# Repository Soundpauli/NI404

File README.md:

DIY OPEN SOURCE HARDWARE SAMPLER-SEQUENCER

---------

IMPORTANT NOTE:

This project, the NI404, is a stale project and is no longer actively maintained. However, it still works and remains an excellent, affordable project for beginners interested in building their own hardware sampler-sequencer. Soldering is required to assemble the NI404. 

For those looking for a more modern alternative, check out the successor project, toern (https://github.com/Soundpauli/toern). The new project offers the option to purchase a self-build kit that doesn't require soldering skills or a fully assembled version. While the NI404 is an older design, feel free to fork the code and contribute to its development if you're interested.

---------

An Etch-A-SketchTM inspired device for beginners and makers.

THE OPEN SOURCE SAMPLE-SEQUENCER FOR EVERYONE.
<<<<<<< HEAD
-------------
The NI404 is an innovative, open-source DIY sample-sequencer from SP_ (aka soundpauli) - inspired by the classic Etch-A-Sketch, tailored for beginners and DIY enthusiasts. Designed around the Teensy Microcontroller and Audioboard from PJRC, this device offers an accessible entry point into the world of music creation.
=======

The NI404 is an innovative, open-source DIY sample-sequencer from SP_ (formaly known as soundpauli) - inspired by the classic Etch-A-Sketch, tailored for beginners and DIY enthusiasts. Designed around the Teensy Microcontroller and Audioboard from PJRC, this device offers an accessible entry point into the world of music creation.
>>>>>>> 7d1964479870bf18bf8a6309d7f64ec11712a006
The NI404 is more than just a musical instrument; it's a journey into the world of sound exploration, perfect for live performances, studio sessions, or simply having fun creating music. Whether you're a seasoned musician or a curious beginner, the NI404 is your gateway to an exciting world of musical possibilities.

EASY TO USE.
-------------
With its playful design, the NI404 lets users create complex sound patterns without any prior knowledge of musical instruments or equipment. It's perfect for beginners and makers alike.

DYNAMIC CONTROL DESPITE LESS BUTTONS.
-------------
At the heart of the NI404 is a vivid 16x16 RGB LED panel display, paired with three intuitive rotary-push encoders. Navigate a cursor across the grid, where each row signifies a voice and each column a potential note, allowing for up to 16 pitches per note. This feature enables the mixing of up to 8 voices simultaneously.

REAL-TIME INTERACTION.
-------------
Adjust samples, instruments, pitches, notes, volume, BPM, velocity, and effects in real-time without pausing. This seamless interaction makes the NI404 an ideal gadget for live performances.

CORE COMPONENTS.
-------------
Teensy 4.1 Microcontroller and Teensy Audio board (4.0)
8MB PSRAM Flash Memory
3 Rotary-push encoders
16x16 RGB-LED Panel driven by FastLED
3.5mm audio jack and removable SD Microcard slot

CREATIVE FLEXIBILITY.
-------------
Etch-A-Sketch style note drawing
On-the-fly note deletion and sample muting
Adjustable volume, BPM (40 - 200), pattern, and note velocity
Up to 30-second sample length with seamless looping
Use your own samples on the SD-Card - in a simple file structure
Load up to 8 voices / samples (Wav format) plus an additional onboard synth voice
16-bar patterns across 8 pages, totaling 128 bars per song
Save and load up to 100 patterns / songs on the SD card
Autosave and autoload functions
SAMPLES AT YOUR FINGERTIPS:
THE BUILT-IN SAMPLE BROWSER.
Access and manage samples while playing, with support for up to 999 samples on the SD card and the ability to predefine multiple voices as a SampleSet.

FULLY INDEPENDENT.
-------------
Operates without a computer, generating all sounds on the device itself. USB powered (5V) and Arduino code is published under the MIT License.

Important: The NI404 does not include speakers or Bluetooth connectivity; Headphones are recommended. Because of licensing: please use your own sample files (folder structure is included).

READY FOR MORE.
-------------
Potential updates include USB-MIDI In & Out, and possible new features you are builing ;)

HARDWARE LIST
-------------
Custom PCB - to connect the encoders to the Teensy (but you can also hard wire everything): see Downloads
1x Teensy 4.1
1x Teensy Audio Adaptor / TEENSY4_AUDIO
2x PSRAM Chip for Teensy 4.1
4x Rotary Encoder KY-040 360degree + Push

Jumper Wire Cables (10cm)
1x Micro SD Card (Class 10)
(Micro SD-Extension)
1x 16x16 RGB LED Matrix

USED LIBRARIES
-------------
WS2812Serial
Teensy Audio Library (Audio.h, v1.0.6)
Quadrature Encoder Library from Paul Stoffregen (Encoder.h, v1.4.4)
Mapf (v1.0.2, GPL-3.0 license)
FastLED (v3.9.10, MIT License)
TeensyPolyphony (v1.0.7, MIT License)

>Important notice:
Dont forget to replace the ResamplingReader.h inside the newdigate/teensy-variable-playback library with the one from this directory - It helps a lot fighting nullptr errors ;)

Compiler-Switches
-------------
USB-Type: (Serial)+MIDI16X

LICENSE
-------------
The code is released under the MIT License, which means it's freely available for personal and commercial use, modification, distribution, and private copying. This permissive license is part of our effort to support innovation and creativity.

However, while the NI404 code itself is under the MIT License, we urge every user to be mindful of the dependencies and libraries utilized within the code. Each of these components may be governed by its own set of licenses. It's crucial for users to verify and ensure that they are in compliance with the licenses of all dependencies and libraries used in their projects. This step is important to respect the legal and ethical frameworks of open-source software.

So, whether you're a seasoned developer or a curious beginner, feel free to dive into the code, explore, modify, and create. Just remember to stay informed and respectful of the licensing requirements of all software components you use.

BUY A NI404
-------------
If you don't like to build your own NI404 (which i would recommend, it's an awesome project even for beginners), you can purchase 
the advances project: TOERN. See toern.live or github for more information.

GRATITUDE
-------------
I would like to extend my heartfelt thanks to Paul Stoffregen and everyone involved at PJRC for their incredible work in creating the Teensy environment and hardware. The innovation and dedication evident in Teensy have significantly impacted the DIY and maker communities, enabling countless creative projects and technological advancements.

Additionally, my gratitude goes out to the broader community of developers and enthusiasts who have contributed libraries for this remarkable piece of hardware. Your collective efforts and shared knowledge have not only enhanced the capabilities of Teensy but have also fostered a spirit of collaboration and open-source development, especially to Nic Newdigate, who contributed the awesome teensy-polyphony library, which is the "soul" of this project. Thanks!

Thank you all for your hard work, ingenuity, and commitment to making the Teensy platform a powerful and accessible tool for creators around the world.

<<<<<<< HEAD
Jan from SP_
=======
Jan from SP_ (formaly known as soundpauli)
>>>>>>> 7d1964479870bf18bf8a6309d7f64ec11712a006
Hamburg, January 2024

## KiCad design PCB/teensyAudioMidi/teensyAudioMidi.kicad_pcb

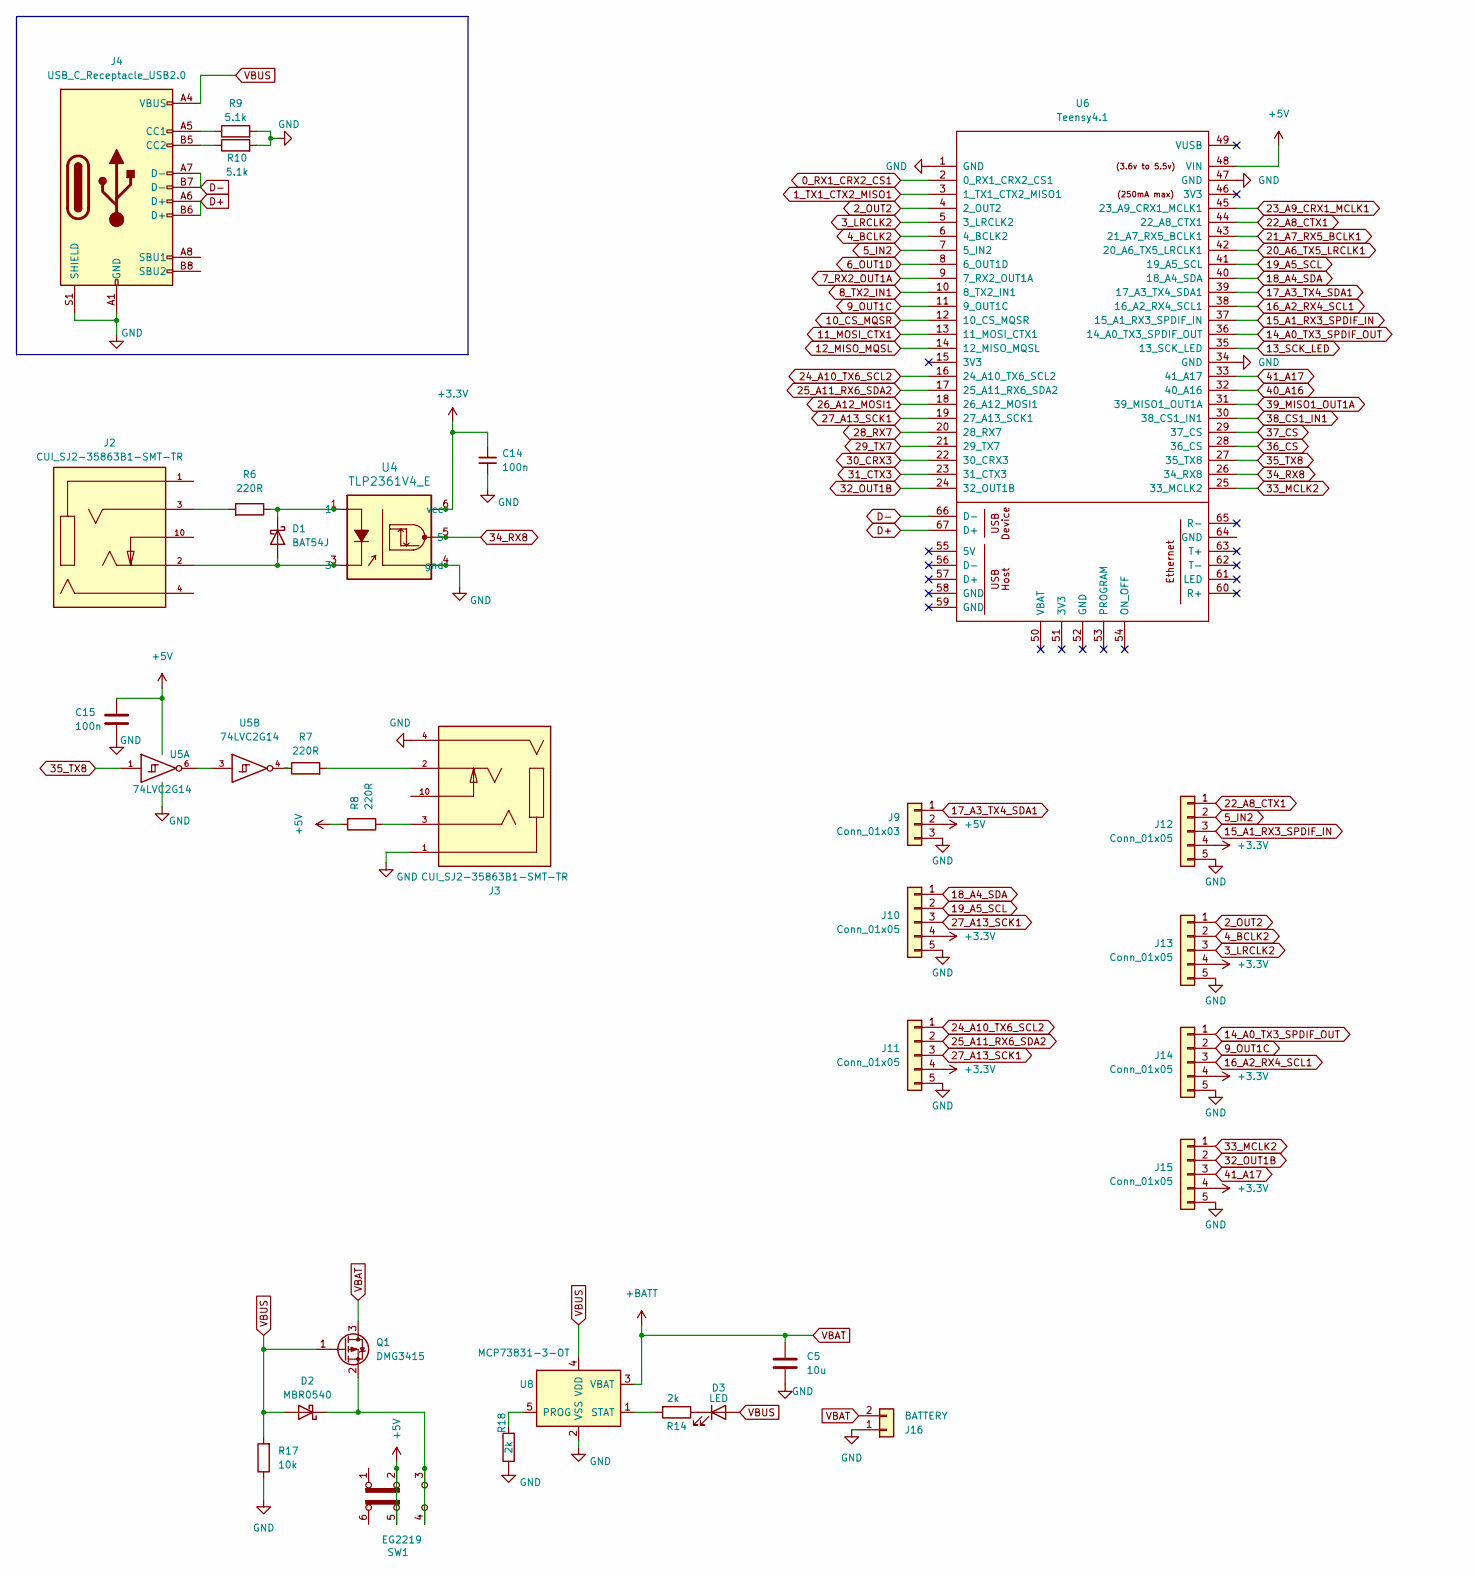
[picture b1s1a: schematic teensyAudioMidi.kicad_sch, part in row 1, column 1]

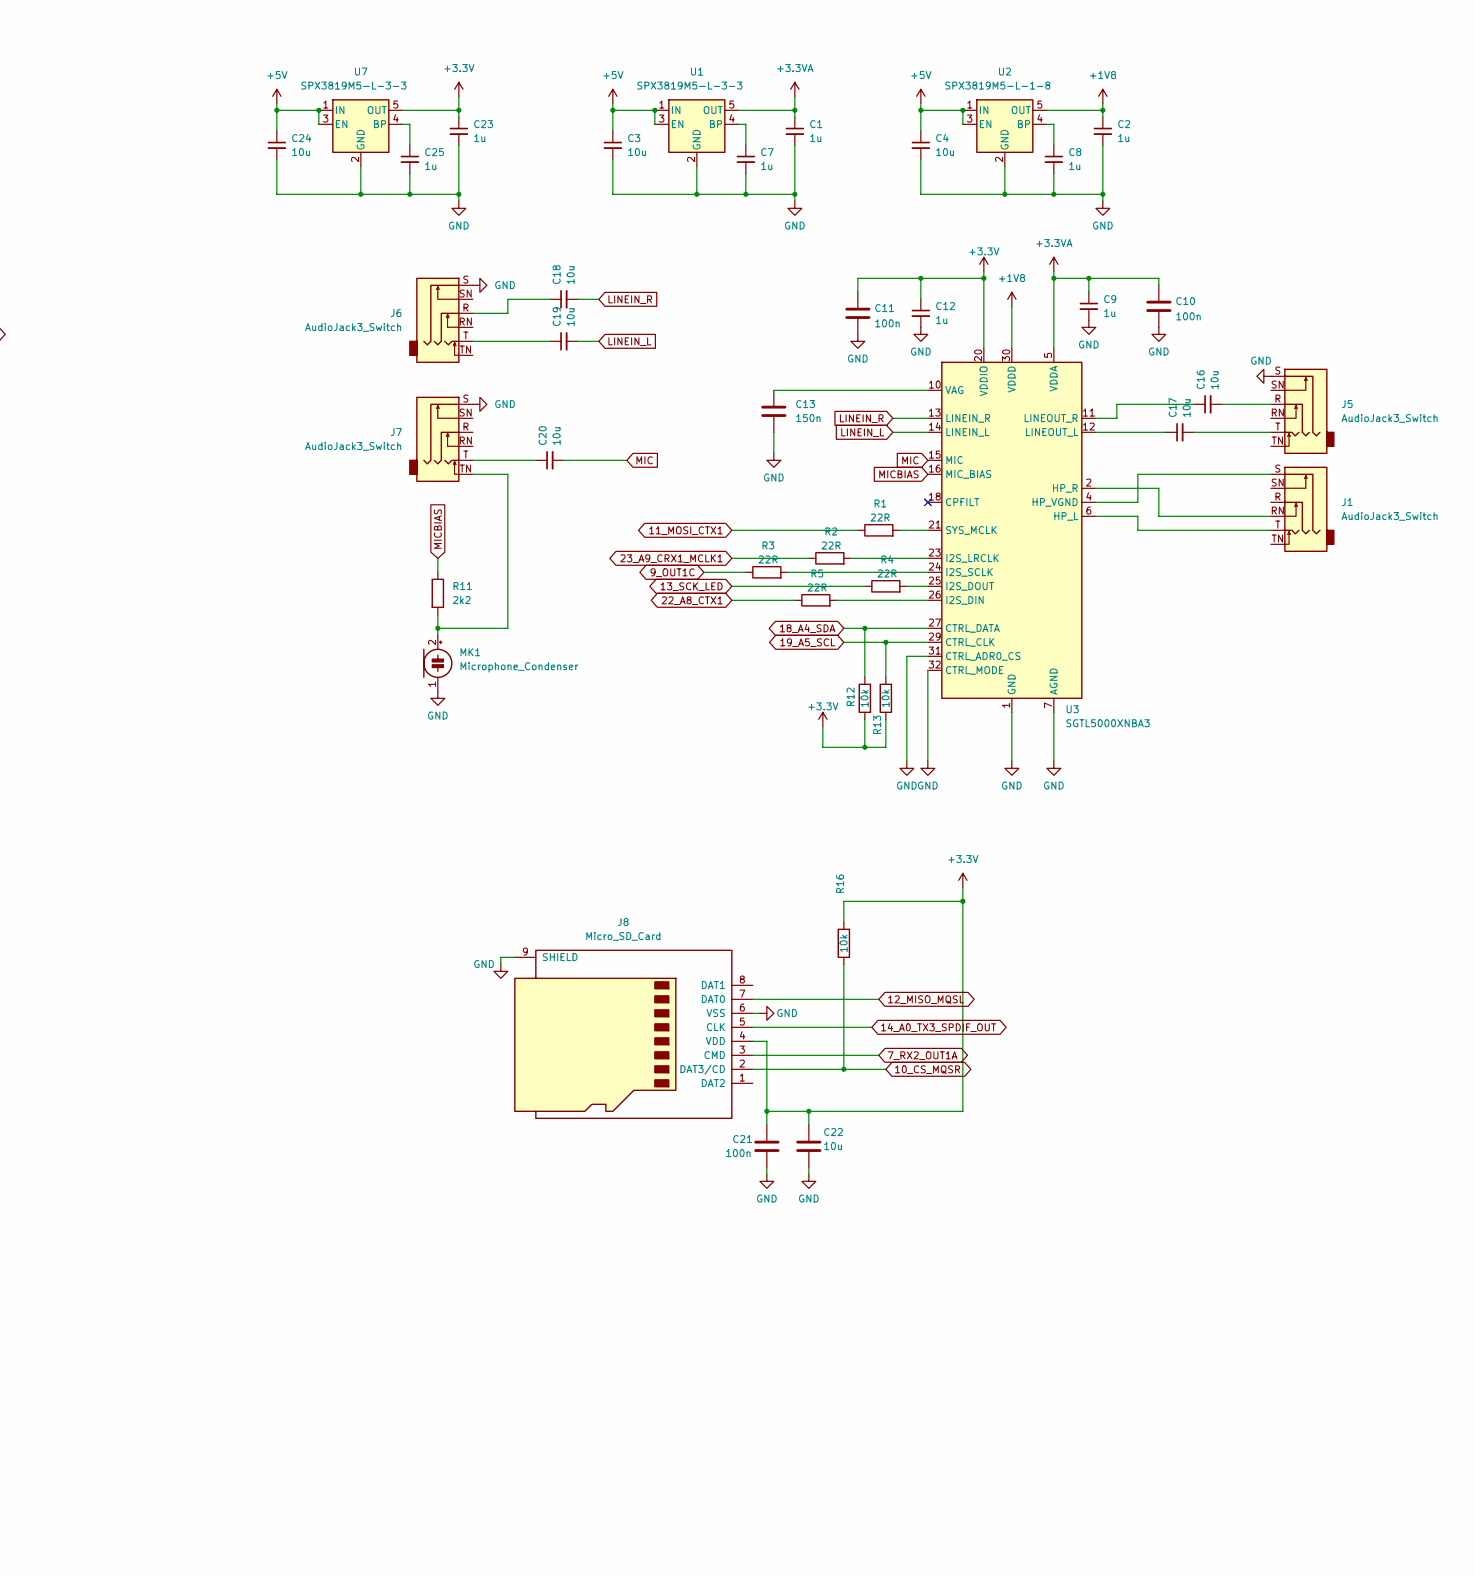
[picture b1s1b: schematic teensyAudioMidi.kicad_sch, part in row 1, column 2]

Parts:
C1, C2, C7, C8, C9, C12, C23, C25: 1u; C_0402_1005Metric; lcsc# C52923
C3, C4, C5, C16, C17, C18, C19, C20, C22, C24: 10u; C_0603_1608Metric; lcsc# C19702
C10, C11: 100n; C_0402_1005Metric; MPN CC0603KRX7R6BB224; lcsc# C77020
C13: 150n; C_0402_1005Metric; lcsc# C162182
C14, C15, C21: 100n; C_0402_1005Metric; lcsc# C77020
D1: BAT54J; D_SOD-323F; lcsc# C130415
D2: MBR0540; D_SOD-123; lcsc# C116159
D3: LED; LED_0603_1608Metric; lcsc# C2286
J1, J5, J6, J7: AudioJack3_Switch; Jack_6.35mm_Neutrik_NMJ6HCD2_Horizontal; lcsc# C368502
J2, J3: CUI_SJ2-35863B1-SMT-TR; PARTREV 1.04; lcsc# C4992707
J4: USB_C_Receptacle_USB2.0; USB_C_Receptacle_HRO_TYPE-C-31-M-12; lcsc# C165948
J8: Micro_SD_Card; microSD_HC_Hirose_DM3BT-DSF-PEJS; lcsc# C597972
J9: Conn_01x03; JST_PH_B3B-PH-K_1x03_P2.00mm_Vertical; lcsc# C131339
J10, J11, J12, J13, J14, J15: Conn_01x05; JST_PH_B5B-PH-K_1x05_P2.00mm_Vertical; lcsc# C157993
J16: BATTERY; JST_PH_B2B-PH-K_1x02_P2.00mm_Vertical; lcsc# C131337
MK1: Microphone_Condenser; POM-2244P-C3310-2-R; lcsc# C3273559
Q1: DMG3415; SOT-23; lcsc# C7202986
R1, R2, R3, R4, R5: 22R; R_0402_1005Metric; lcsc# C25092
R6, R7, R8: 220R; R_0603_1608Metric; lcsc# C22962
R9, R10: 5.1k; R_0402_1005Metric; lcsc# C25905
R11: 2k2; R_0603_1608Metric; lcsc# C4190
R12, R13, R16, R17: 10k; R_0402_1005Metric; lcsc# C98220
R14, R18: 2k; R_0603_1608Metric; lcsc# C22975
SW1: EG2219; lcsc# C3664594
U1, U7: SPX3819M5-L-3-3; SOT-23-5; lcsc# C9055
U2: SPX3819M5-L-1-8; SOT-23-5; lcsc# C24639
U3: SGTL5000XNBA3; QFN-32-1EP_5x5mm_P0.5mm_EP3.6x3.6mm; lcsc# C5196742
U4: TLP2361V4_E; 5pin SO6_TOS; lcsc# C107626
U5: 74LVC2G14; SOT-23-6; LCSC Part # C12401
U6: Teensy4.1; Teensy41; lcsc# ----
U8: MCP73831-3-OT; SOT-23-5; lcsc# C14879

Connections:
0_RX1_CRX2_CS1: U6.2 (0_RX1_CRX2_CS1)
1_TX1_CTX2_MISO1: U6.3 (1_TX1_CTX2_MISO1)
2_OUT2: J13.1, U6.4 (2_OUT2)
3_LRCLK2: J13.3, U6.5 (3_LRCLK2)
4_BCLK2: J13.2, U6.6 (4_BCLK2)
5_IN2: J12.2, U6.7 (5_IN2)
6_OUT1D: U6.8 (6_OUT1D)
7_RX2_OUT1A: J8.3 (CMD), U6.9 (7_RX2_OUT1A)
8_TX2_IN1: U6.10 (8_TX2_IN1)
9_OUT1C: J14.2, R3.1, U6.11 (9_OUT1C)
10_CS_MQSR: J8.2 (DAT3/CD), R16.1, U6.12 (10_CS_MQSR)
11_MOSI_CTX1: R1.1, U6.13 (11_MOSI_CTX1)
12_MISO_MQSL: J8.7 (DAT0), U6.14 (12_MISO_MQSL)
13_SCK_LED: R4.1, U6.35 (13_SCK_LED)
14_A0_TX3_SPDIF_OUT: J8.5 (CLK), J14.1, U6.36 (14_A0_TX3_SPDIF_OUT)
15_A1_RX3_SPDIF_IN: J12.3, U6.37 (15_A1_RX3_SPDIF_IN)
16_A2_RX4_SCL1: J14.3, U6.38 (16_A2_RX4_SCL1)
17_A3_TX4_SDA1: J9.1, U6.39 (17_A3_TX4_SDA1)
18_A4_SDA: J10.1, R12.2, U3.27 (CTRL_DATA), U6.40 (18_A4_SDA)
19_A5_SCL: J10.2, R13.2, U3.29 (CTRL_CLK), U6.41 (19_A5_SCL)
20_A6_TX5_LRCLK1: U6.42 (20_A6_TX5_LRCLK1)
21_A7_RX5_BCLK1: U6.43 (21_A7_RX5_BCLK1)
22_A8_CTX1: J12.1, R5.1, U6.44 (22_A8_CTX1)
23_A9_CRX1_MCLK1: R2.1, U6.45 (23_A9_CRX1_MCLK1)
24_A10_TX6_SCL2: J11.1, U6.16 (24_A10_TX6_SCL2)
25_A11_RX6_SDA2: J11.2, U6.17 (25_A11_RX6_SDA2)
26_A12_MOSI1: U6.18 (26_A12_MOSI1)
27_A13_SCK1: J10.3, J11.3, U6.19 (27_A13_SCK1)
28_RX7: U6.20 (28_RX7)
29_TX7: U6.21 (29_TX7)
30_CRX3: U6.22 (30_CRX3)
31_CTX3: U6.23 (31_CTX3)
32_OUT1B: J15.2, U6.24 (32_OUT1B)
33_MCLK2: J15.1, U6.25 (33_MCLK2)
34_RX8: U4.5, U6.26 (34_RX8)
35_TX8: U5.1, U6.27 (35_TX8)
36_CS: U6.28 (36_CS)
37_CS: U6.29 (37_CS)
38_CS1_IN1: U6.30 (38_CS1_IN1)
39_MISO1_OUT1A: U6.31 (39_MISO1_OUT1A)
40_A16: U6.32 (40_A16)
41_A17: J15.3, U6.33 (41_A17)
+1V8: C2.1, U2.5 (OUT), U3.30 (VDDD)
+3.3V: C11.1, C12.1, C14.2, C21.2, C22.1, C23.1, J8.4 (VDD), J10.4, J11.4, J12.4, J13.4, J14.4, J15.4, R12.1, R13.1, R16.2, U3.20 (VDDIO), U4.6 (vcc), U7.5 (OUT)
+3.3VA: C1.1, C9.1, C10.1, U1.5 (OUT), U3.5 (VDDA)
+5V: C3.1, C4.1, C15.1, C24.1, J9.2, R8.2, SW1.2 (B), SW1.5 (B), U1.1 (IN), U1.3 (EN), U2.1 (IN), U2.3 (EN), U5.5 (VCC), U6.48 (VIN), U7.1 (IN), U7.3 (EN)
D+: J4.A6 (D+), J4.B6 (D+), U6.67 (D+)
D-: J4.A7 (D-), J4.B7 (D-), U6.66 (D-)
GND: C1.2, C2.2, C3.2, C4.2, C5.2, C7.2, C8.2, C9.2, C10.2, C11.2, C12.2, C13.2, C14.1, C15.2, C21.1, C22.2, C23.2, C24.2, C25.2, J3.1, J3.4, J4.A1 (GND), J4.A12 (GND), J4.B1 (GND), J4.B12 (GND), J4.S1 (SHIELD), J5.S, J6.S, J7.S, J8.6 (VSS), J8.9 (SHIELD), J9.3, J10.5, J11.5, J12.5, J13.5, J14.5, J15.5, J16.1, MK1.1 (-), R9.2, R10.2, R17.1, R18.1, U1.2 (GND), U2.2 (GND), U3.1 (GND), U3.3 (GND), U3.7 (AGND), U3.31 (CTRL_ADR0_CS), U3.32 (CTRL_MODE), U3.33 (GND), U4.4 (gnd), U5.2 (GND), U6.1 (GND), U6.34 (GND), U6.47 (GND), U7.2 (GND), U8.2 (VSS)
LINEIN_L: C19.2, U3.14 (LINEIN_L)
LINEIN_R: C18.2, U3.13 (LINEIN_R)
MIC: C20.2, U3.15 (MIC)
MICBIAS: R11.1, U3.16 (MIC_BIAS)
unnamed: C16.2, J5.R
unnamed: C17.2, J5.T
unnamed: C18.1, J6.R
unnamed: C19.1, J6.T
unnamed: C20.1, J7.T
unnamed: D1.2 (A), J2.2, U4.3
unnamed: D1.1 (K), R6.1, U4.1
unnamed: D2.1 (K), Q1.2 (S), SW1.3 (C), SW1.4 (A)
unnamed: D3.1 (K), R14.1
unnamed: J2.3, R6.2
unnamed: J3.2, R7.2
unnamed: J3.3, R8.1
unnamed: J4.A5 (CC1), R9.1
unnamed: J4.B5 (CC2), R10.1
unnamed: J7.TN, MK1.2 (+), R11.2
unnamed: R7.1, U5.4
unnamed: C7.1, U1.4 (BP)
unnamed: C8.1, U2.4 (BP)
unnamed: J1.T, U3.6 (HP_L)
unnamed: J1.RN, U3.2 (HP_R)
unnamed: J1.S, U3.4 (HP_VGND)
unnamed: R5.2, U3.26 (I2S_DIN)
unnamed: R4.2, U3.25 (I2S_DOUT)
unnamed: R2.2, U3.23 (I2S_LRCLK)
unnamed: R3.2, U3.24 (I2S_SCLK)
unnamed: C17.1, U3.12 (LINEOUT_L)
unnamed: C16.1, U3.11 (LINEOUT_R)
unnamed: R1.2, U3.21 (SYS_MCLK)
unnamed: C13.1, U3.10 (VAG)
unnamed: U5.3, U5.6
unnamed: C25.1, U7.4 (BP)
unnamed: R18.2, U8.5 (PROG)
unnamed: R14.2, U8.1 (STAT)
VBAT: C5.1, J16.2, Q1.3 (D), U8.3 (VBAT)
VBUS: D2.2 (A), D3.2 (A), J4.A4 (VBUS), J4.A9 (VBUS), J4.B4 (VBUS), J4.B9 (VBUS), Q1.1 (G), R17.2, U8.4 (VDD)

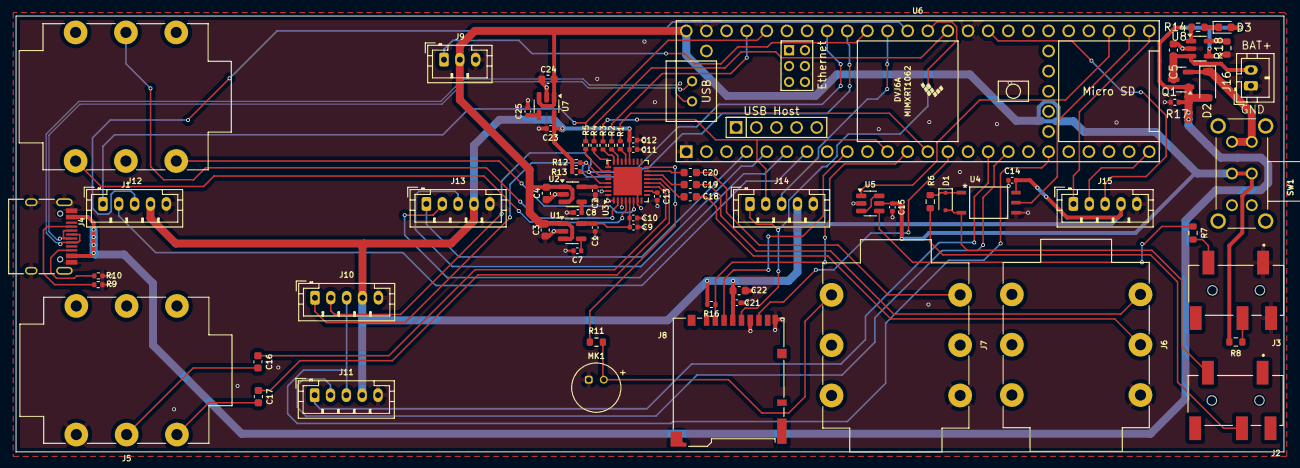
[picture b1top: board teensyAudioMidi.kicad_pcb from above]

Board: 4 copper layers, 160.0 x 55.0 mm, 71 parts (0 on the bottom side), 72 nets.

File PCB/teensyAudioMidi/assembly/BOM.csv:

Designator,Comment,Footprint,LCSC Part #
"C1,C2,C7,C8,C9,C12,C23,C25",1u,Capacitor_SMD:C_0402_1005Metric,C52923
"C3,C4,C5,C16,C17,C18,C19,C20,C22,C24",10u,Capacitor_SMD:C_0603_1608Metric,C19702
"C10,C11,C14,C15,C21",100n,Capacitor_SMD:C_0402_1005Metric,C77020
C13,150n,Capacitor_SMD:C_0402_1005Metric,C162182
D1,BAT54J,Diode_SMD:D_SOD-323F,C130415
D2,MBR0540,Diode_SMD:D_SOD-123,C116159
D3,LED,LED_SMD:LED_0603_1608Metric,C2286
"J1,J5,J6,J7",AudioJack3_Switch,Connector_Audio:Jack_6.35mm_Neutrik_NMJ6HCD2_Horizontal,C368502
"J2,J3",CUI_SJ2-35863B1-SMT-TR,myLibKicad:CUI_SJ2-35863B1-SMT-TR,C4992707
J4,USB_C_Receptacle_USB2.0,Connector_USB:USB_C_Receptacle_HRO_TYPE-C-31-M-12,C165948
J8,Micro_SD_Card,Connector_Card:microSD_HC_Hirose_DM3BT-DSF-PEJS,C597972
J9,Conn_01x03,Connector_JST:JST_PH_B3B-PH-K_1x03_P2.00mm_Vertical,C131339
"J10,J11,J12,J13,J14,J15",Conn_01x05,Connector_JST:JST_PH_B5B-PH-K_1x05_P2.00mm_Vertical,C157993
J16,BATTERY,Connector_JST:JST_PH_B2B-PH-K_1x02_P2.00mm_Vertical,C131337
MK1,Microphone_Condenser,Sensor_Audio:POM-2244P-C3310-2-R,C3273559
Q1,DMG3415,Package_TO_SOT_SMD:SOT-23,C7202986
"R1,R2,R3,R4,R5",22R,Resistor_SMD:R_0402_1005Metric,C25092
"R6,R7,R8",220R,Resistor_SMD:R_0603_1608Metric,C22962
"R9,R10",5.1k,Resistor_SMD:R_0402_1005Metric,C25905
R11,2k2,Resistor_SMD:R_0603_1608Metric,C4190
"R12,R13,R16,R17",10k,Resistor_SMD:R_0402_1005Metric,C98220
"R14,R18",2k,Resistor_SMD:R_0603_1608Metric,C22975
SW1,EG2219,myLibKicad:EG2219,C3664594
"U1,U7",SPX3819M5-L-3-3,Package_TO_SOT_SMD:SOT-23-5,C9055
U2,SPX3819M5-L-1-8,Package_TO_SOT_SMD:SOT-23-5,C24639
U3,SGTL5000XNBA3,Package_DFN_QFN:QFN-32-1EP_5x5mm_P0.5mm_EP3.6x3.6mm, C5196742
U4,TLP2361V4_E,myLibKicad:5pin SO6_TOS,C107626
U5,74LVC2G14,Package_TO_SOT_SMD:SOT-23-6,C12401
U6,Teensy4.1,myLibKicad:Teensy41,----
U8,MCP73831-3-OT,Package_TO_SOT_SMD:SOT-23-5,C14879

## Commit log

2024-01-21 Rename Readme.md to README.md
2024-01-25 add usbMidi input and bugfix for scrolling left on pages
2024-01-28 added stl files of housing
2024-08-27 complete refactor
2024-08-28 fixed noteShifting
2024-08-28 fixed noteShifting and velocity
2024-08-30 fixed autoload and sampleload
2024-11-10 refactor2: filebrowser, memory, fx, load, save, play
2024-11-13 fixed filebrowser for multiple channels
2024-11-13 removed history from git
2025-01-08 removed PCB because failures
2025-02-04 added PCB and final code
2025-02-04 updated files, new pcb
2025-02-04 updated files
2025-02-04 added housing 3d and dxf
2025-02-04 removed unused files
2025-02-07 cleaned up files
2025-02-07 cleaned up files2
2025-02-07 cleaned up files3
2025-02-07 cleaned up files4
2025-05-23 added build files + HEX
